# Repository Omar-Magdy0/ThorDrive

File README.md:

---
# ⚡ ThorDrive

A modular, open-source platform for developing **inverters**, **controllers**, and **embedded firmware** for electric vehicle applications.  
Built with robust engineering principles and driven by passion.

Maintained by **Omar Magdy** for the **Cairo University Eco Racing Team**.

---

## 🧠 Overview

ThorDrive implements a range of hardware and software solutions for electric drive systems.  
It includes:

- Custom inverters (multi-phase and bidirectional support)
- Firmware for Trapezoidal , FOC, SPWM, SVM, and advanced motor control
- Modular controllers and drivers
- Fully documented software and hardware stacks
- Design iterations built for real-world racing

---

## 🚀 Features

- ⚙️ **Multiple Inverter Designs**
- 🧾 **Well-documented Firmware** using Doxygen
- 💡 **Modular & Scalable Design** across generations
- 🛠️ **Interactive BOMs and Fabrication-Ready Gerbers**
- 🔧 **Configurable Build System** for firmware
- 💻 **Simulator & HIL Support**
- 🧪 **Validated by Real-World Team Use**

Specific features are documented in each design subfolder:

## 🛠️ Get Started

1. **Navigate to a Design Folder**  
   Visit:
   - `ThorDrive_FW/<DesignName_and_Version>/README.md`
   - `ThorDrive_HW/<DesignName_and_Version>/README.md`

2. **Build Software / Flash Firmware**  
   Follow platform-specific build instructions in each firmware README.

3. **Hardware Fabrication**  
   - Use provided **Gerber** files for PCB manufacturing.
   - Access **Interactive BOM** from each hardware directory.

---

## 📚 Documentation

- **Firmware Documentation (Doxygen)**  
  Inside:  
  `ThorDrive_FW/<DesignName_and_Version>/docs/index.html`

- **Hardware Documentation**  
  - Inverter: `ThorDrive_HW/<DesignName_and_Version>/Inverter/Docs/`
  - Controller: `ThorDrive_HW/<DesignName_and_Version>/Controller/Docs/`

---

## 📦 Installation

- Build your own firmware using the instructions in each firmware folder.
- Or, download the **precompiled binaries** from the design folders.
- Configure and flash using the README-provided instructions.

---

## 🧑‍💻 Used By

- 🏁 **Cairo University Eco Racing Team** https://cu-eco.org

---

## 📄 License

This project is open source.  
📌 **License**:  MIT

---

## 💬 Support

You can support the project by:

- Contributing firmware or hardware improvements
- Reviewing documentation and build systems
- Participating in issue tracking and pull requests
- Providing feedback based on hardware tests
- Become a sponsor
---

## 🤝 Sponsors

- 🐚 **Shell**
- ✈️ **EgyptAir**

---

## 📬 Contact

Maintainer: **Omar Magdy**  
📧 [omar.magdy.om.om@gmail.com](mailto:omar.magdy.om.om@gmail.com)

---

## 🏷️ Acknowledgements

- All engineers and contributors from the Cairo University Eco Racing Team

---

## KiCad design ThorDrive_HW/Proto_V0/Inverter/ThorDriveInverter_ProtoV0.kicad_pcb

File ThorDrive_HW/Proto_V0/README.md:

📁 `Controller`

# 🧠 BLDC Controller Board

---

## 🔁 Version & Overview

* **Version:** `v1.0`
* **Microcontroller:** `ATmega328P`
* **Designed using:** `KiCad`

The controller board enables BLDC motor control using ATmega328P and supports BEMF zero-crossing sensorless operation.

---

## 🔧 Features

* Sensorless BLDC drive (BEMF zero crossing)
* UART debugging
* Modular firmware architecture
* Supports 3.3V and 5V I/O
* Optimized for low-cost, compact embedded motor controllers
* Single-layer board with minimal top jumpers

#### Notes 
Remove onBoard Potentiometer if going to install external Potentiometer

---

## 🖼️ Hardware Preview

---

## 📁 Documentation

| Type            | Path            |
| --------------- | --------------- |
| 🧩 3D Model     | `./Controller/Docs/*.step` |
| 📝 Schematic    | `./Controller/Docs/*.pdf`  |
| 📂 Design Files | `./Controller`            |

### 🌐 Embedded 3D Viewer (STEP)

Try with: [https://3dviewer.net/](https://3dviewer.net/)
Upload: [`./Controller/Docs/*.step`](./Docs)

---

📁 `Inverter`

# ⚡ BLDC Inverter Board

---

## 🔁 Version & Overview

* **Version:** `v1.0`
* **Designed using:** `KiCad`
* **Power Rating:** `2KW+`
* **MOSFET Driver:** `IR2130`

---

## 🔧 Features

### ✅ Phase Voltage Feedback

* Each phase is conditioned via:

  $V_{cond} = V_{phase-ground} \times \left(\frac{2.2k}{49.2k}\right)$

* Filtered with **80kHz low-pass**

* Calibrate as needed due to resistor tolerances

### ✅ Line Current Feedback (ACS712-30A)

* For Phase A & B:

  $V_{cond} = \left( I_{line} \times 66\text{mV} + 2.5 \right) \times \left(\frac{5.1k}{15.1k}\right)$

* Filtered with **80kHz low-pass**

* Calibrate as needed due to resistor tolerances

### ✅ &#x20;General Specs

* 3.3V signal compatible
* Switching frequency up to **20kHz**
* Driver with built-in **dead time** (IR2130)
* 🌡️ **Thermal Management**: Adequate spacing for heat sinks
* Single-layer board with minimal top jumpers

---

## 🖼️ Hardware Preview

---

## 📁 Documentation

| Type            | Path            |
| --------------- | --------------- |
| 🧩 3D Model     | `./Inverter/Docs/*.step` |
| 📝 Schematic    | `./Inverter/Docs/*.pdf`  |
| 📂 Design Files | `./Inverter`            |

### 🌐 Embedded 3D Viewer (STEP)

Try with: [https://3dviewer.net/](https://3dviewer.net/)
Upload: [`Docs/*.step`](./Docs)

---

## 🔌 Connector Layout & Wiring
Proper connector pin labeling is essential for integration with other subsystems (sensors, MCU, battery, etc.). Images and pinout illustrations will help ensure correct assembly.

### 📷 Visual Reference
 #### 📍 Connector Numbering Reference
<!-- Replace with your actual images -->
**JST**

**Molex**

🔌 Sample Harness:  

---

## 📜 License

This project is licensed under the **MIT License**.
---

## 📬 Contact

Maintainer: **Omar Magdy**
📧 [omar.magdy.om.om@gmail.com](mailto:omar.magdy.om.om@gmail.com)

---

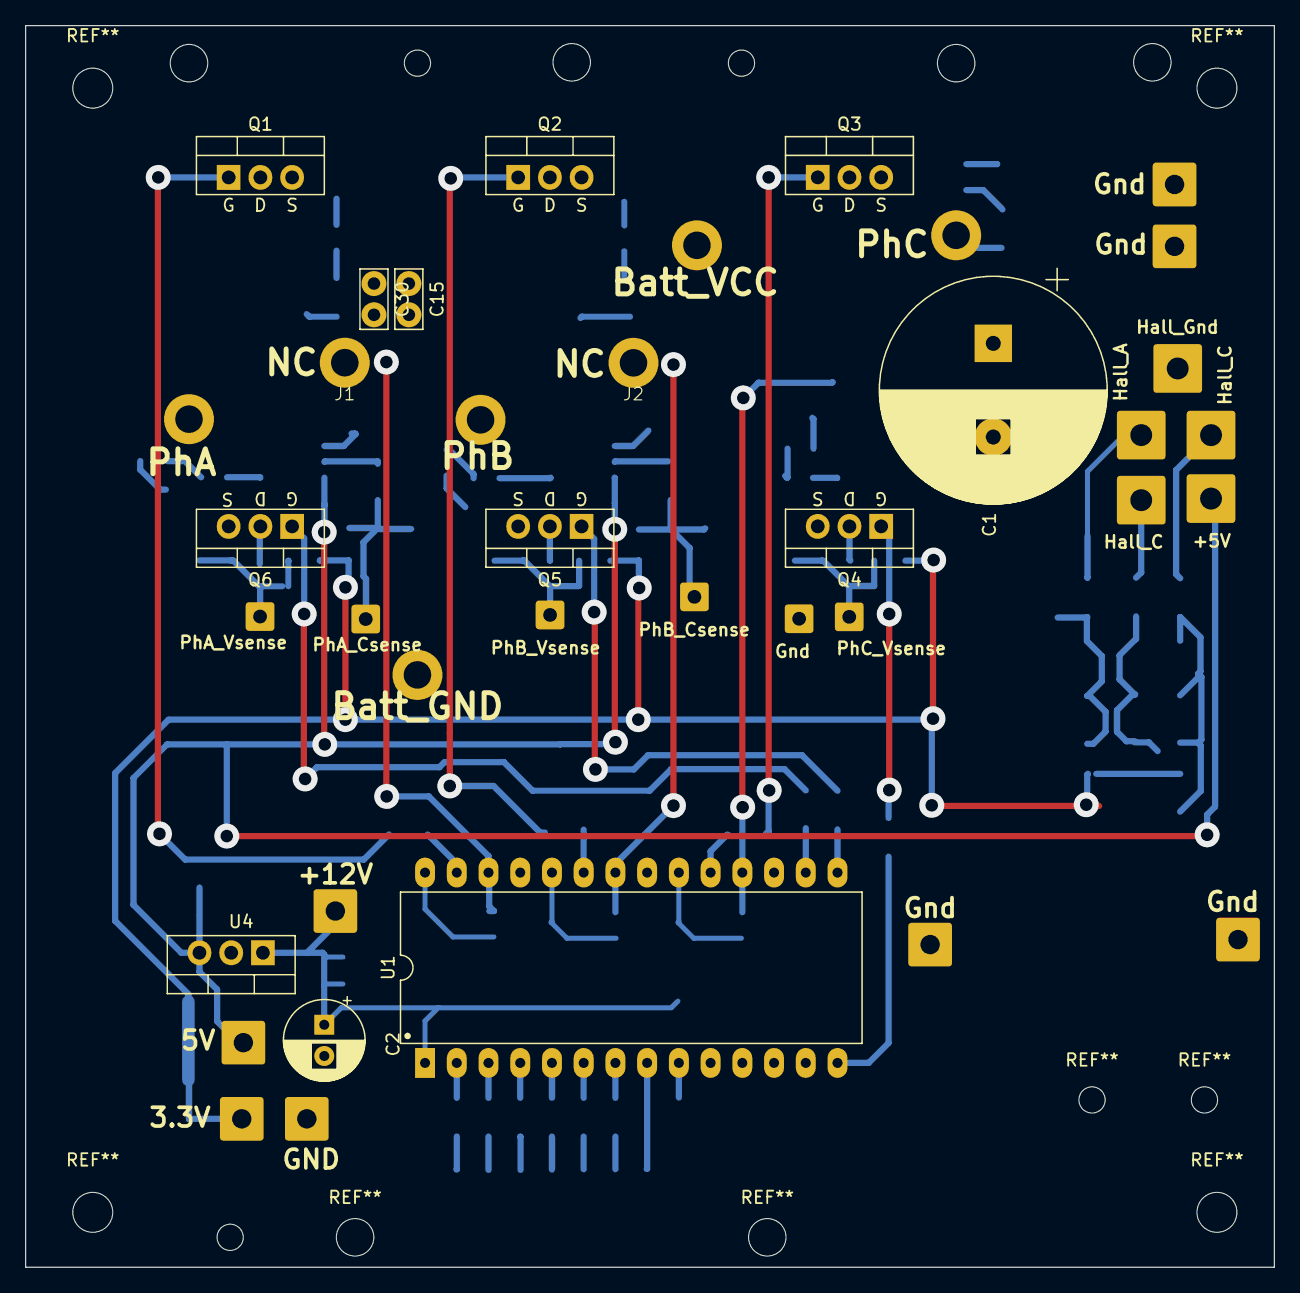
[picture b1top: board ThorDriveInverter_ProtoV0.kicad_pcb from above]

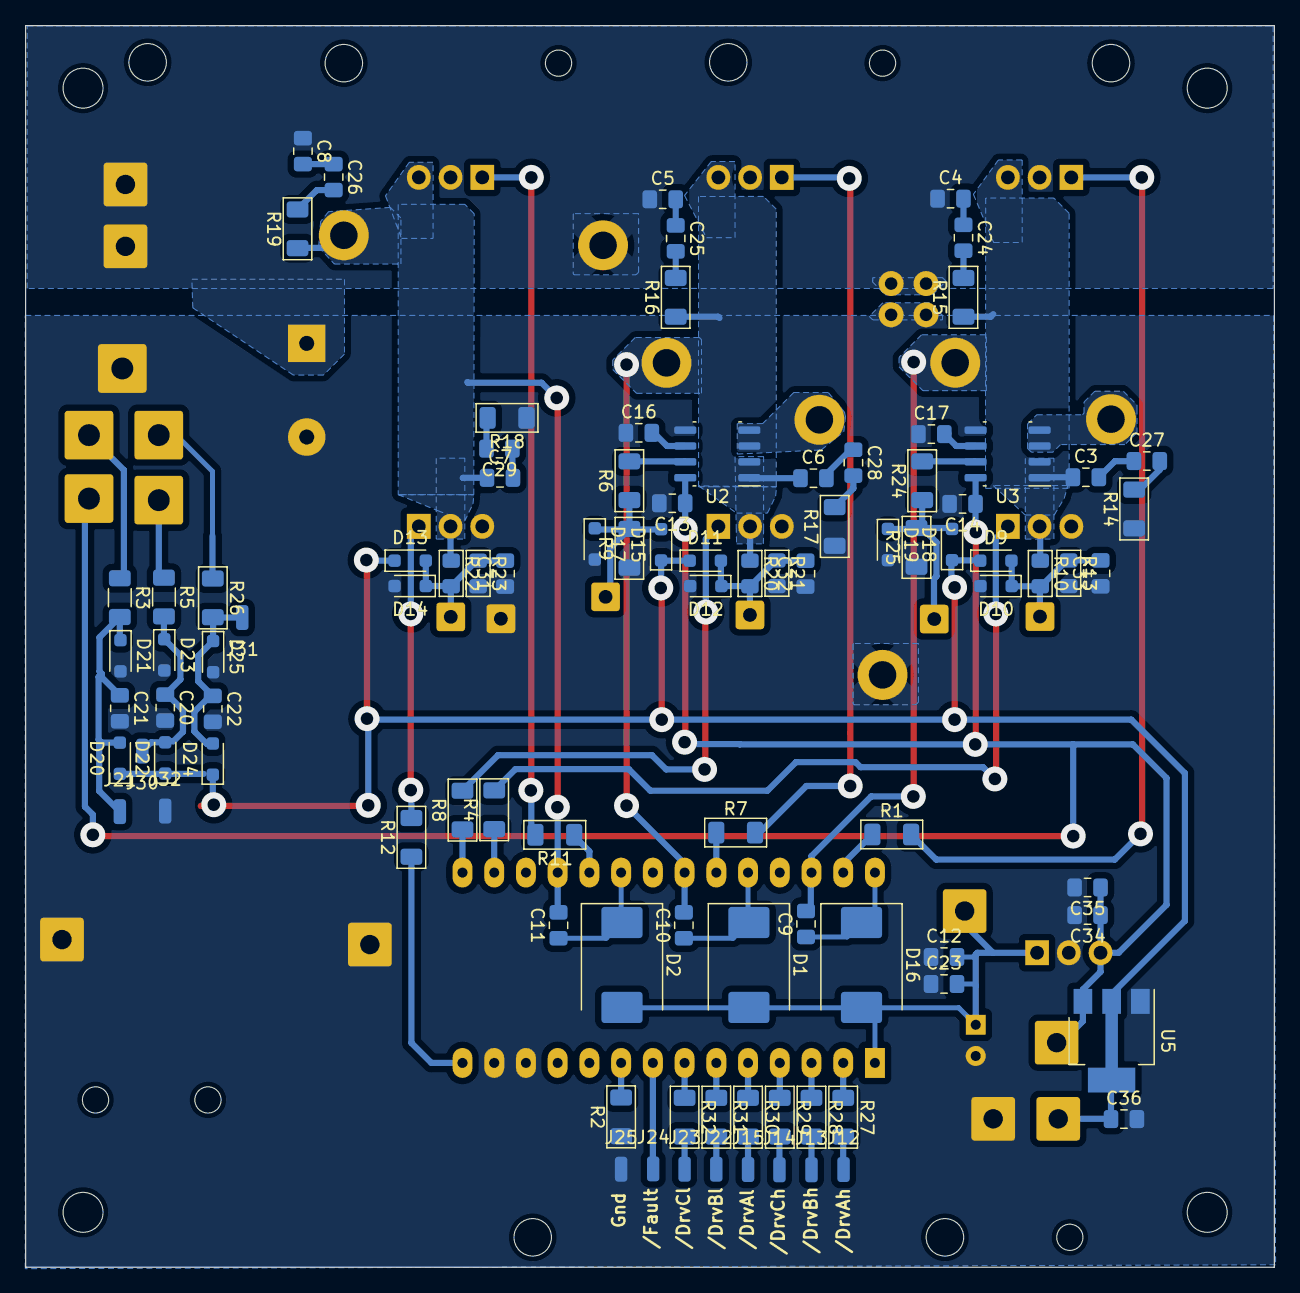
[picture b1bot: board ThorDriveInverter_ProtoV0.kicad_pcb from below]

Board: 2 copper layers, 100.0 x 99.4 mm, 128 parts (96 on the bottom side), 66 nets.

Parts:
+5V: SolderWire-1sqmm_1x01_D1.4mm_OD3.9mm
+12V: 15Vin; SolderWire-0.75sqmm_1x01_D1.25mm_OD3.5mm
Batt_GND: Bat Gnd; 12AWG cableSoldered
Batt_VCC: Bat VCC; 12AWG cableSoldered
C1: 470uF; CP_Radial_D18.0mm_P7.50mm
C2: 22uF; CP_Radial_D6.3mm_P2.50mm
C3, C4, C5, C6, C7, C8, C24, C25, C26, C27, C28, C29: 4.7nF; C_0805_2012Metric_Pad1.18x1.45mm_HandSolder
C9, C10, C11, C12, C34, C35, C36: 2.2uF; C_0805_2012Metric_Pad1.18x1.45mm_HandSolder
C13, C14, C23: 0.1uF; C_0805_2012Metric_Pad1.18x1.45mm_HandSolder
C15, C30: 2.2uF; C_Rect_L4.6mm_W2.0mm_P2.50mm_MKS02_FKP02
C16, C17, C31, C32, C33: 1nF; C_0805_2012Metric_Pad1.18x1.45mm_HandSolder
C20, C21, C22: 10nF; C_0805_2012Metric_Pad1.18x1.45mm_HandSolder
D1, D2, D16: SS310; D_SMC
D9, D10, D11, D12, D13, D14, D15, D17, D18, D19, D20, D21, D22, D23, D24, D25: SD103AWS; D_SOD-323_HandSoldering
Gnd: 15 Gnd; SolderWire-0.75sqmm_1x01_D1.25mm_OD3.5mm
Gnd#2: GND0_sense; SolderWire-0.5sqmm_1x01_D0.9mm_OD2.3mm
Hall_A: SolderWire-1sqmm_1x01_D1.4mm_OD3.9mm
Hall_C: SolderWire-1sqmm_1x01_D1.4mm_OD3.9mm
Hall_C#2: SolderWire-1sqmm_1x01_D1.4mm_OD3.9mm
Hall_Gnd: SolderWire-1sqmm_1x01_D1.4mm_OD3.9mm
J1: Motor_phaseA; 10mm2 CableSoldered
J2: Motor_phaseB; 10mm2 CableSoldered
J12, J13, J14, J15, J21, J22, J23, J24, J25, J30, J31, J32: SolderWirePad_1x01_SMD_1x2mm
PhA: Motor_phaseASensed; 10mm2 CableSoldered
PhA_Csense: PhaseA_Csense; SolderWire-0.5sqmm_1x01_D0.9mm_OD2.3mm
PhA_Vsense: PhaseA_Vsense; SolderWire-0.5sqmm_1x01_D0.9mm_OD2.3mm
PhB: Motor_phaseBSensed; 10mm2 CableSoldered
PhB_Csense: PhaseB_Csense; SolderWire-0.5sqmm_1x01_D0.9mm_OD2.3mm
PhB_Vsense: PhaseB_Vsense; SolderWire-0.5sqmm_1x01_D0.9mm_OD2.3mm
PhC: Motor_phaseC; 10mm2 CableSoldered
PhC_Vsense: PhaseC_Vsense; SolderWire-0.5sqmm_1x01_D0.9mm_OD2.3mm
Q1, Q2, Q3, Q4, Q5, Q6: IRF1407; TO-220-3_Vertical_GDS
R1, R4, R7, R8, R11, R12: 15; R_1206_3216Metric_Pad1.30x1.75mm_HandSolder
R2: 10k; R_1206_3216Metric_Pad1.30x1.75mm_HandSolder
R3, R5, R14, R15, R16, R17, R18, R19, R26: 100; R_1206_3216Metric_Pad1.30x1.75mm_HandSolder
R6, R24: 5K; R_1206_3216Metric_Pad1.30x1.75mm_HandSolder
R9, R25: 10K; R_1206_3216Metric_Pad1.30x1.75mm_HandSolder
R10, R20, R22: 47K; R_0805_2012Metric_Pad1.15x1.40mm_HandSolder
R13, R21, R23: 2.2k; R_0805_2012Metric_Pad1.15x1.40mm_HandSolder
R27, R28, R29, R30, R31, R32: 470; R_1206_3216Metric_Pad1.30x1.75mm_HandSolder
U1: IR2130PBF; DIP-28_W15.24mm_LongPads
U2, U3: ACS712ELCTR30AT; SOIC-8-1EP_3.9x4.9mm_P1.27mm_EP2.95x4.9mm_Mask2.71x3.4mm
U4: LM7805_TO220; TO-220-3_Vertical
U5: AMS1117-3.3; SOT-223-3_TabPin2

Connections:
+3.3V: C36.1, D9.1 (K), D11.1 (K), D13.1 (K), D15.1 (K), D18.1 (K), D20.1 (K), D22.1 (K), D24.1 (K), U5.2 (VO)
+5V: +5V.1, C13.1, C14.1, C34.1, C35.1, U2.8 (VCC), U3.8 (VCC), U4.3 (VO), U5.3 (VI)
+15V: +12V.1, C2.1, C12.2, C23.2, D1.2 (A), D2.2 (A), D16.2 (A), U1.1 (VCC), U4.1 (VI)
+BATT: Batt_VCC.1, C1.1, C4.1, C5.1, C8.1, C15.1, C30.1, Q1.2 (D), Q2.2 (D), Q3.2 (D)
/Connectors/HSensor1: Hall_C.1, R3.1
/Connectors/HSensor1_ToMCU: C21.1, D20.2 (A), D21.1 (K), J21.1, R3.2
/Connectors/HSensor2: Hall_C#2.1, R5.1
/Connectors/HSensor2_ToMCU: C20.1, D22.2 (A), D23.1 (K), J30.1, R5.2
/Connectors/HSensor3: Hall_A.1, R26.1
/Connectors/HSensor3_ToMCU: C22.1, D24.2 (A), D25.1 (K), J31.1, R26.2
GND: Batt_GND.1, C1.2, C2.2, C12.1, C13.2, C14.2, C15.2, C16.1, C17.1, C20.2, C21.2, C22.2, C23.1, C30.2, C31.1, C32.1, C33.1, C34.2, C35.2, C36.2, D10.2 (A), D12.2 (A), D14.2 (A), D17.2 (A), D19.2 (A), D21.2 (A), D23.2 (A), D25.2 (A), Gnd.1, Gnd#2.1, Hall_Gnd.1, J25.1, J32.1, Q4.3 (S), Q5.3 (S), Q6.3 (S), R2.1, R9.1, R13.2, R14.1, R17.1, R18.1, R21.2, R23.2, R25.1, U1.12 (VSS), U1.13 (VS0), U2.5 (GND), U3.5 (GND), U4.2 (GND), U5.1 (GND)
Isense_PhaseA: R24.2, U3.7 (VIOUT)
Isense_PhaseB: R6.2, U2.7 (VIOUT)
L1H: R1.1, U1.27 (HO1)
L1L: R4.1, U1.16 (LO1)
L2H: R7.1, U1.23 (HO2)
L2L: R8.1, U1.15 (LO2)
L3H: R11.1, U1.19 (HO3)
L3L: R12.1, U1.14 (LO3)
LOGIC_L1H: J12.1, R27.2
LOGIC_L1L: J15.1, R30.2
LOGIC_L2H: J13.1, R28.2
LOGIC_L2L: J22.1, R31.2
LOGIC_L3H: J14.1, R29.2
LOGIC_L3L: J23.1, R32.2
MCU_FAULT_IN (INPUT_PULLUP): J24.1, U1.8 (*FAULT)
unnamed: C4.2, C24.1
unnamed: C24.2, R15.2
unnamed: C5.2, C25.1
unnamed: C25.2, R16.2
unnamed: C8.2, C26.1
unnamed: C26.2, R19.2
unnamed: C3.2, C27.1
unnamed: C27.2, R14.2
unnamed: C6.2, C28.1
unnamed: C28.2, R17.2
unnamed: C7.2, C29.1
unnamed: C29.2, R18.2
unnamed: C33.2, D9.2 (A), D10.1 (K), PhA_Vsense.1, R10.2, R13.1
unnamed: C32.2, D11.2 (A), D12.1 (K), PhB_Vsense.1, R20.2, R21.1
unnamed: C31.2, D13.2 (A), D14.1 (K), PhC_Vsense.1, R22.2, R23.1
unnamed: D15.2 (A), D17.1 (K), PhB_Csense.1, R6.1, R9.2
unnamed: D18.2 (A), D19.1 (K), PhA_Csense.1, R24.1, R25.2
unnamed: Q1.1 (G), R1.2
unnamed: Q2.1 (G), R7.2
unnamed: Q3.1 (G), R11.2
unnamed: Q4.1 (G), R12.2
unnamed: Q5.1 (G), R8.2
unnamed: Q6.1 (G), R4.2
unnamed: R27.1, U1.2 (*HIN1)
unnamed: R28.1, U1.3 (*HIN2)
unnamed: R29.1, U1.4 (*HIN3)
unnamed: R30.1, U1.5 (*LIN1)
unnamed: R31.1, U1.6 (*LIN2)
unnamed: R32.1, U1.7 (*LIN3)
unnamed: R2.2, U1.9 (ITRIP)
unnamed: C16.2, U2.6 (FILTER)
unnamed: C17.2, U3.6 (FILTER)
PhaseA: C3.1, C9.2, J1.1, Q1.3 (S), Q6.2 (D), R10.1, R15.1, U1.26 (VS1), U3.1 (IP+), U3.2 (IP+)
PhaseA_Sensed: PhA.1, U3.3 (IP-), U3.4 (IP-)
PhaseB: C6.1, C10.2, J2.1, Q2.3 (S), Q5.2 (D), R16.1, R20.1, U1.22 (VS2), U2.1 (IP+), U2.2 (IP+)
PhaseB_Sensed: PhB.1, U2.3 (IP-), U2.4 (IP-)
PhaseC: C7.1, C11.2, PhC.1, Q3.3 (S), Q4.2 (D), R19.1, R22.1, U1.18 (VS3)
VBOOT1: C9.1, D16.1 (K), U1.28 (VB1)
VBOOT2: C10.1, D1.1 (K), U1.24 (VB2)
VBOOT3: C11.1, D2.1 (K), U1.20 (VB3)

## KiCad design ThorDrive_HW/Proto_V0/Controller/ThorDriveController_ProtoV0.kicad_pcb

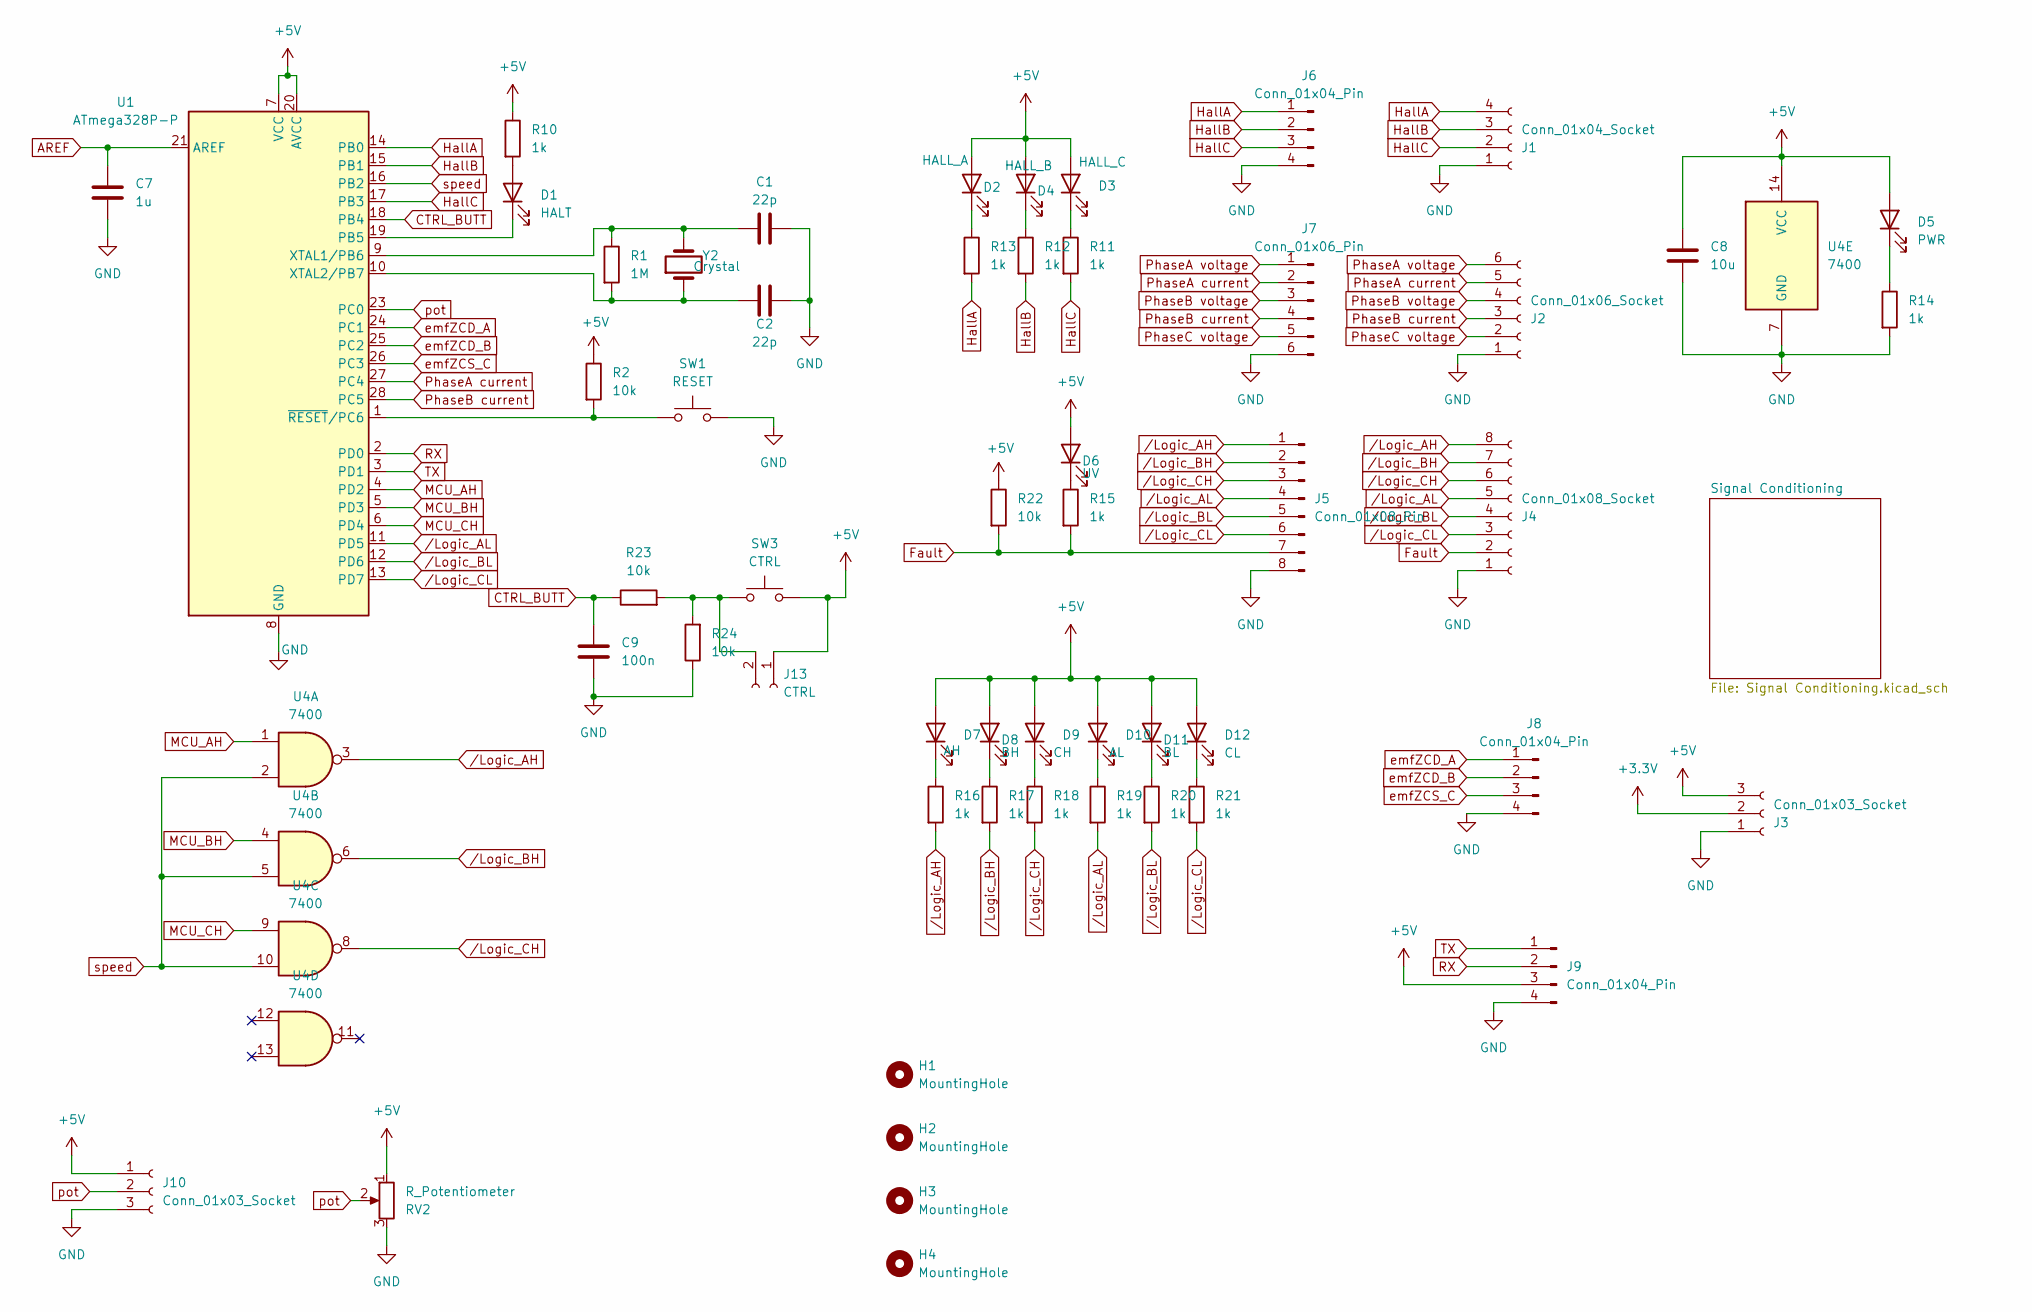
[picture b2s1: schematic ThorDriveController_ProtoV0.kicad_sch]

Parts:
C1, C2: 22p; C_0805_2012Metric_Pad1.18x1.45mm_HandSolder
C7: 1u; C_0805_2012Metric_Pad1.18x1.45mm_HandSolder
C8: 10u; C_0805_2012Metric_Pad1.18x1.45mm_HandSolder
C9: 100n; C_0805_2012Metric_Pad1.18x1.45mm_HandSolder
D1: HALT; LED_D3.0mm
D2: HALL_A; LED_D3.0mm
D3: HALL_C; LED_D3.0mm
D4: HALL_B; LED_D3.0mm
D5: PWR; LED_D3.0mm
D6: UV; LED_D3.0mm
D7: AH; LED_D3.0mm
D8: BH; LED_D3.0mm
D9: CH; LED_D3.0mm
D10: AL; LED_D3.0mm
D11: BL; LED_D3.0mm
D12: CL; LED_D3.0mm
H1, H2, H3, H4: MountingHole; MountingHole_3.2mm_M3
J1: Conn_01x04_Socket; JST_EH_B4B-EH-A_1x04_P2.50mm_Vertical
J2: Conn_01x06_Socket; JST_EH_B6B-EH-A_1x06_P2.50mm_Vertical
J3, J10: Conn_01x03_Socket; JST_EH_B3B-EH-A_1x03_P2.50mm_Vertical
J4: Conn_01x08_Socket; JST_EH_B8B-EH-A_1x08_P2.50mm_Vertical
J5: Conn_01x08_Pin; PinHeader_1x08_P2.54mm_Vertical
J6, J8, J9: Conn_01x04_Pin; PinHeader_1x04_P2.54mm_Vertical
J7: Conn_01x06_Pin; PinHeader_1x06_P2.54mm_Vertical
J13: CTRL; JST_EH_B2B-EH-A_1x02_P2.50mm_Vertical
R1: 1M; R_1206_3216Metric_Pad1.30x1.75mm_HandSolder
R2, R22, R23, R24: 10k; R_1206_3216Metric_Pad1.30x1.75mm_HandSolder
R10, R11, R12, R13, R14, R15, R16, R17, R18, R19, R20, R21: 1k; R_0805_2012Metric_Pad1.20x1.40mm_HandSolder
RV2: R_Potentiometer; Potentiometer_Piher_T-16H_Single_Horizontal
SW1: RESET; SW_BUTT-2
SW3: CTRL; SW_BUTT-2
U1: ATmega328P-P; DIP-28_W7.62mm
U4: 7400; SOIC-14_3.9x8.7mm_P1.27mm
Y2: Crystal; Crystal_HC49-4H_Vertical

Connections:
+3.3V: J3.2
+5V: C8.1, D2.2 (A), D3.2 (A), D4.2 (A), D5.2 (A), D6.2 (A), D7.2 (A), D8.2 (A), D9.2 (A), D10.2 (A), D11.2 (A), D12.2 (A), J3.3, J9.3, J10.1, J13.1, R2.1, R10.1, R22.1, RV2.1, SW3.2, U1.7 (VCC), U1.20 (AVCC), U4.14 (VCC); also elsewhere on the board
AREF: C7.1, U1.21 (AREF)
CTRL_BUTT: C9.1, R23.1, U1.18 (PB4)
Fault: J4.2, J5.7, R15.2, R22.2
GND: C1.2, C2.2, C7.2, C8.2, C9.2, J1.1, J2.1, J3.1, J4.1, J5.8, J6.4, J7.6, J8.4, J9.4, J10.3, R14.2, R24.1, RV2.3, SW1.2, U1.8 (GND), U1.22 (GND), U4.7 (GND); also elsewhere on the board
HallA: J1.4, J6.1, R13.2, U1.14 (PB0)
HallB: J1.3, J6.2, R12.2, U1.15 (PB1)
HallC: J1.2, J6.3, R11.2, U1.17 (PB3)
MCU_AH: U1.4 (PD2), U4.1
MCU_BH: U1.5 (PD3), U4.4
MCU_CH: U1.6 (PD4), U4.9
unnamed: D1.2 (A), R10.2
unnamed: D1.1 (K), U1.19 (PB5)
unnamed: D2.1 (K), R13.1
unnamed: D3.1 (K), R11.1
unnamed: D4.1 (K), R12.1
unnamed: D5.1 (K), R14.1
unnamed: D6.1 (K), R15.1
unnamed: D7.1 (K), R16.1
unnamed: D8.1 (K), R17.1
unnamed: D9.1 (K), R18.1
unnamed: D10.1 (K), R19.1
unnamed: D11.1 (K), R20.1
unnamed: D12.1 (K), R21.1
unnamed: J13.2, R23.2, R24.2, SW3.1
unnamed: C1.1, R1.1, U1.9 (XTAL1/PB6), Y2.2
unnamed: C2.1, R1.2, U1.10 (XTAL2/PB7), Y2.1
unnamed: R2.2, SW1.1, U1.1 (~RESET/PC6)
PhaseA current: J2.5, J7.2, U1.27 (PC4)
PhaseA voltage: J2.6, J7.1; also elsewhere on the board
PhaseB current: J2.3, J7.4, U1.28 (PC5)
PhaseB voltage: J2.4, J7.3; also elsewhere on the board
PhaseC voltage: J2.2, J7.5; also elsewhere on the board
RX: J9.2, U1.2 (PD0)
TX: J9.1, U1.3 (PD1)
emfZCD_A: J8.1, U1.24 (PC1); also elsewhere on the board
emfZCD_B: J8.2, U1.25 (PC2); also elsewhere on the board
emfZCS_C: J8.3, U1.26 (PC3); also elsewhere on the board
pot: J10.2, RV2.2, U1.23 (PC0)
speed: U1.16 (PB2), U4.2, U4.5, U4.10
/Logic_AH: J4.8, J5.1, R16.2, U4.3
/Logic_AL: J4.5, J5.4, R19.2, U1.11 (PD5)
/Logic_BH: J4.7, J5.2, R17.2, U4.6
/Logic_BL: J4.4, J5.5, R20.2, U1.12 (PD6)
/Logic_CH: J4.6, J5.3, R18.2, U4.8
/Logic_CL: J4.3, J5.6, R21.2, U1.13 (PD7)

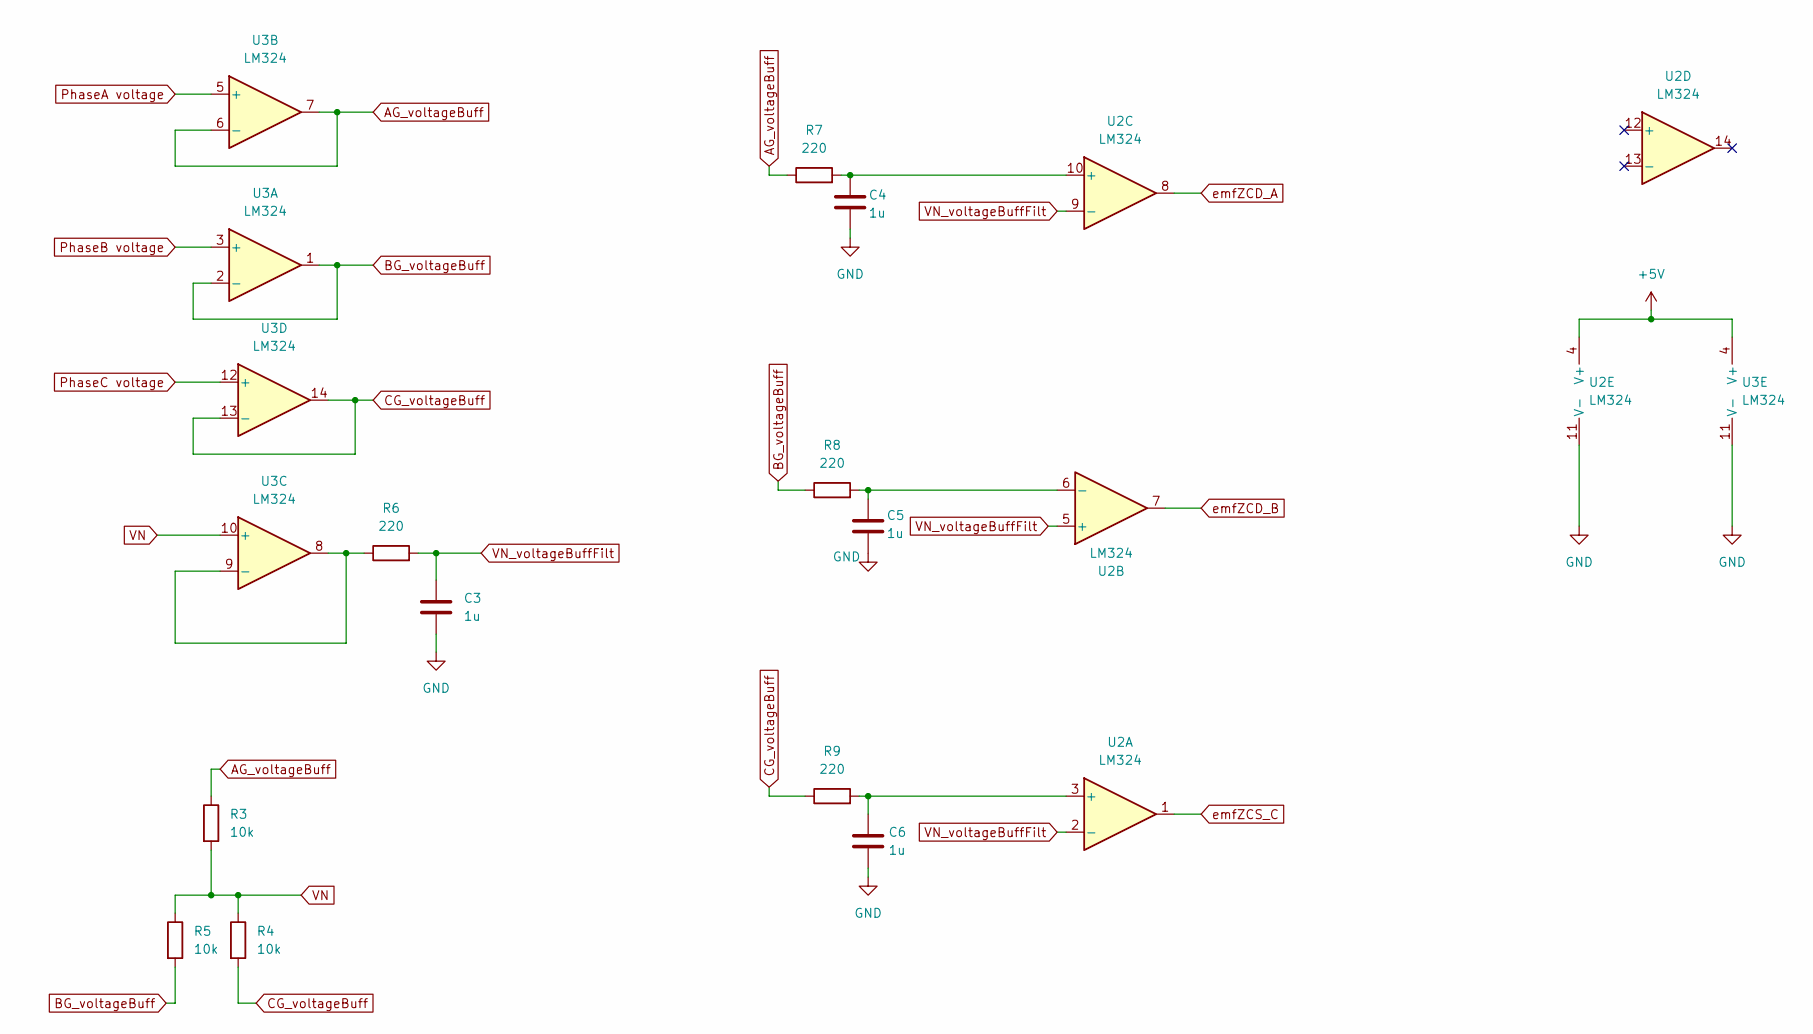
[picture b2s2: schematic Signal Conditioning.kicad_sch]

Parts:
C3, C4, C5, C6: 1u; C_0805_2012Metric_Pad1.18x1.45mm_HandSolder
R3, R4, R5: 10k; R_1206_3216Metric_Pad1.30x1.75mm_HandSolder
R6, R7, R8, R9: 220; R_0805_2012Metric_Pad1.20x1.40mm_HandSolder
U2, U3: LM324; SOIC-14_3.9x8.7mm_P1.27mm

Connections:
+5V: U2.4 (V+), U3.4 (V+); also elsewhere on the board
AG_voltageBuff: R3.1, R7.1, U3.6 (-), U3.7
BG_voltageBuff: R5.2, R8.1, U3.1, U3.2 (-)
CG_voltageBuff: R4.2, R9.1, U3.13 (-), U3.14
GND: C3.2, C4.2, C5.2, C6.2, U2.11 (V-), U3.11 (V-); also elsewhere on the board
unnamed: C6.1, R9.2, U2.3 (+)
unnamed: C5.1, R8.2, U2.6 (-)
unnamed: C4.1, R7.2, U2.10 (+)
unnamed: R6.1, U3.8, U3.9 (-)
PhaseA voltage: U3.5 (+); also elsewhere on the board
PhaseB voltage: U3.3 (+); also elsewhere on the board
PhaseC voltage: U3.12 (+); also elsewhere on the board
VN: R3.2, R4.1, R5.1, U3.10 (+)
VN_voltageBuffFilt: C3.1, R6.2, U2.2 (-), U2.5 (+), U2.9 (-)
emfZCD_A: U2.8; also elsewhere on the board
emfZCD_B: U2.7; also elsewhere on the board
emfZCS_C: U2.1; also elsewhere on the board

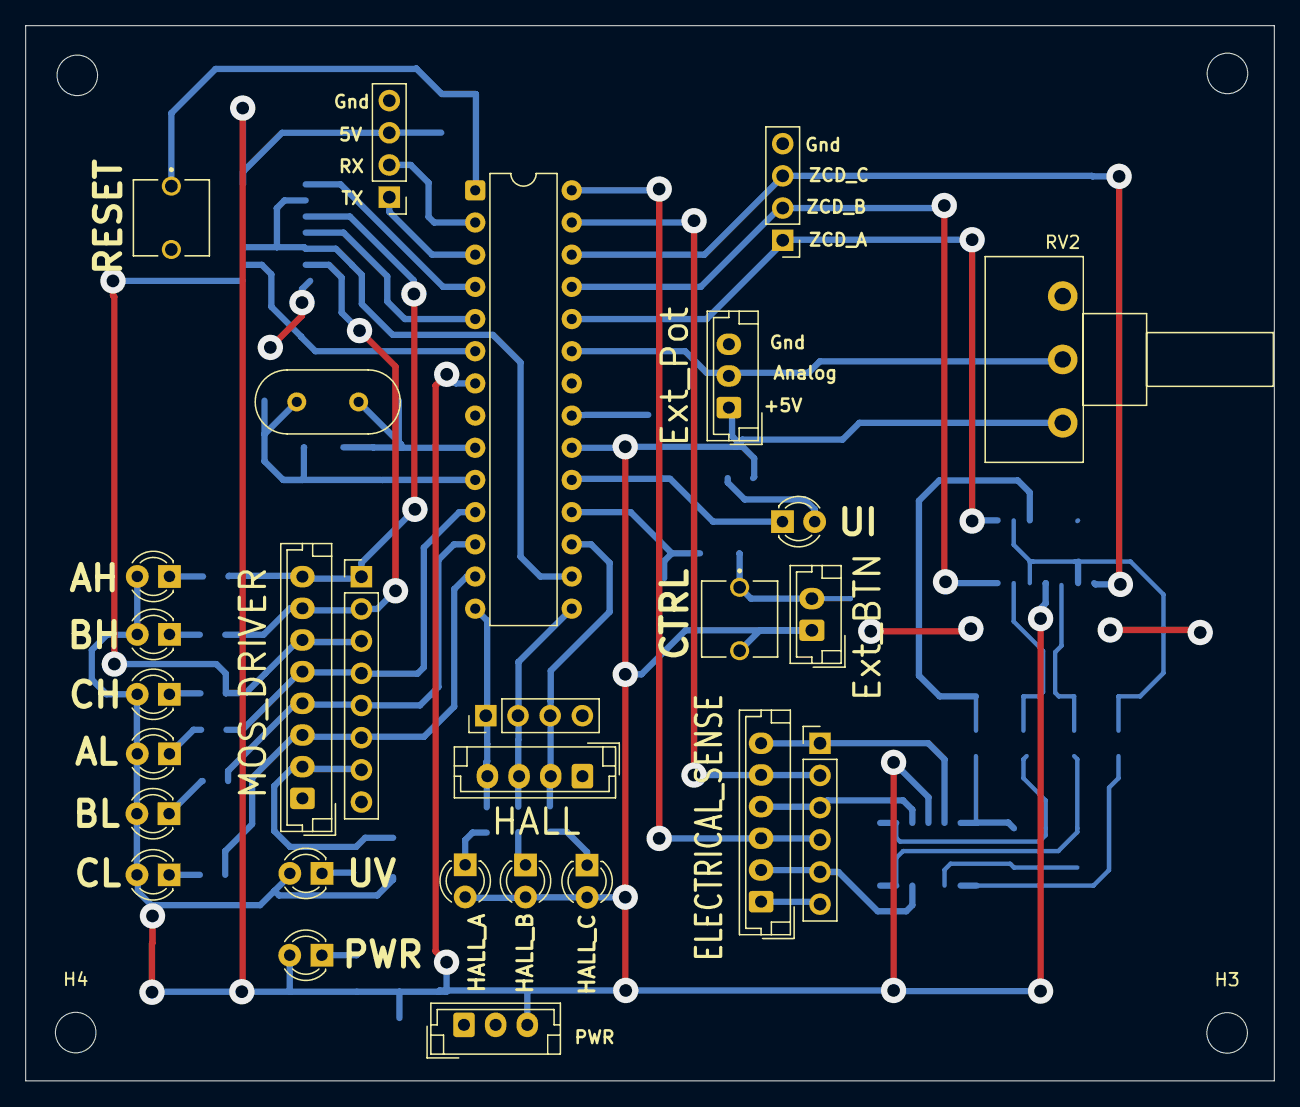
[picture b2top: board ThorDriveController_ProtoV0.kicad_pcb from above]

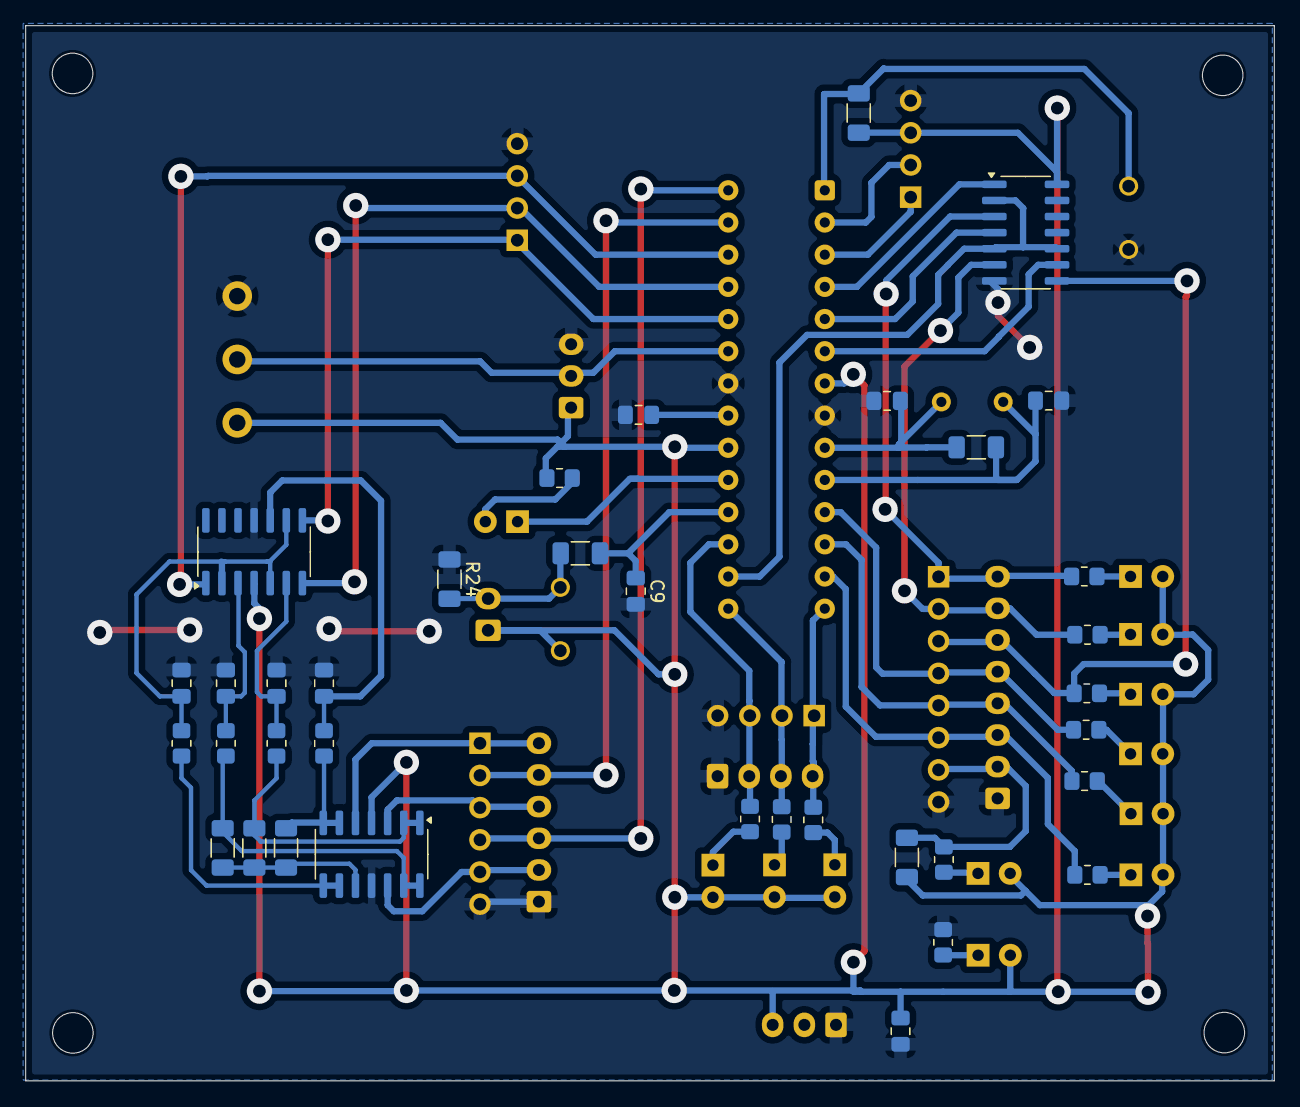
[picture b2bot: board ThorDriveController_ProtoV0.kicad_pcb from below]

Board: 2 copper layers, 98.5 x 83.3 mm, 68 parts (36 on the bottom side), 55 nets.

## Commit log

2025-06-09 Initial Repo Config and Fw files
    *Added platformIO project
    *Added Proteus Simulation project for Atmega328p
2025-06-15 Firmware and Hardware Initials
2025-06-16 Routing Try0
2025-06-16 Controller Board V0 Finalized
    A Controller Board simple and built upon the Atmega328p...
    Single Layer Design with few jumpers.... Compatible with Inverter V0
2025-06-16 Added GPIO struct and Modified PWM driver
2025-06-19 Latest hardware changes (added pulldown Resistor for CTRL button)
2025-06-22 Added Basic Drivers, Initialized system manager
2025-06-26 initialized
2025-06-28 Added Hardware Documentation and reference Designs..... Added Software template and multiple modules
2025-07-10 Enforced design patterns
    Clean Design
